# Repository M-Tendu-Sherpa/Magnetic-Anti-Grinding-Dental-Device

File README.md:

# Magnetic-Anti-Grinding-Dental-Device
This project is associated with the granted U.S. patent:
US12011386B1 — Magnetic anti-grinding dental device, system, and method
https://patents.google.com/patent/US12011386B1/en

I served as a co‑inventor and owned the end‑to‑end electrical hardware development, including architecture, schematic capture, PCB layout, embedded firmware, prototype bring‑up, and hardware validation.

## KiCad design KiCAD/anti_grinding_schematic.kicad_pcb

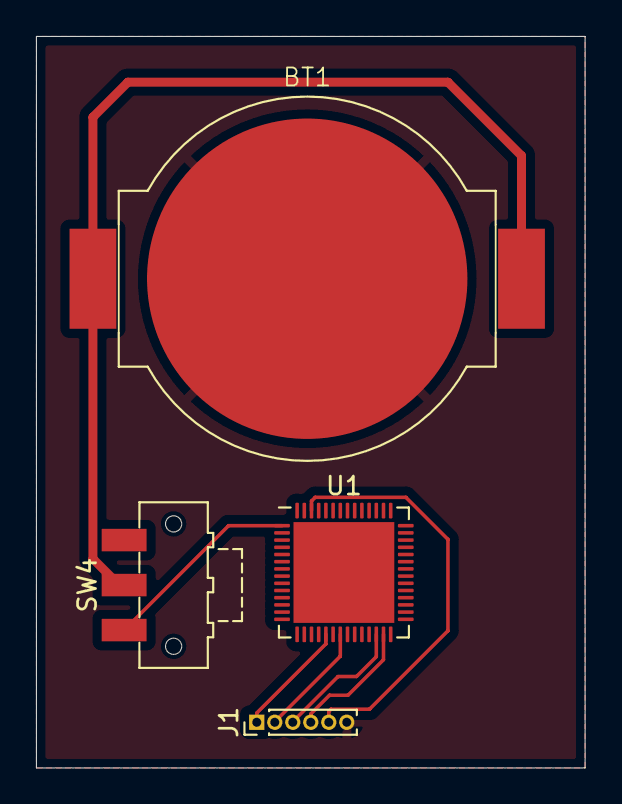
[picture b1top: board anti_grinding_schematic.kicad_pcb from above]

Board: 2 copper layers, 30.5 x 40.6 mm, 4 parts (0 on the bottom side), 8 nets.

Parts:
BT1: Battery_Cell; BatteryHolder_MPD_BC2003_1x2032
J1: Conn_01x06_Pin; PinHeader_1x06_P1.00mm_Vertical
SW4: PWR_SW; SW_SPDT_CK-JS102011SAQN
U1: CY8C4xx7LQI-4xx; QFN-56-1EP_7x7mm_P0.4mm_EP5.6x5.6mm

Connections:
GND: BT1.2 (-), J1.6, U1.9 (VSSD)
unnamed: BT1.1 (+), SW4.2 (B)
unnamed: J1.1, U1.19 (P0.0)
unnamed: J1.2, U1.21 (P0.2)
unnamed: J1.3, U1.26 (P0.6)
unnamed: J1.4, U1.27 (P0.7)
unnamed: SW4.1 (A), U1.1 (VDDD)
Solenoid: J1.5, U1.54 (P3.7)
